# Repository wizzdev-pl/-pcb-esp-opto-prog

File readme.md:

# ESP Optoisolated Programmer

This repo contains design files of the ESP Optoisolated Programmer. It is helpful to develop software for products with and ESP microcontroller that are powered from 230V mains. It works for ESP32, ESP8266 and all other ESP modules.

For detailed description please read:
- [Schematic Description 1](https://wizzdev.pl/blog/esp32-optoisolated-programmer-schematic-description-1/)
- [Schematic Description 2](https://wizzdev.pl/blog/esp32-optoisolated-programmer-schematic-description-2/)
- [PCB Analysis 1](https://wizzdev.pl/blog/esp32-optoisolated-programmer-pcb-analysis-1-2/)
- [PCB Analysis 2](https://wizzdev.pl/blog/esp32-optoisolated-programmer-pcb-analysis-2/)
- [PCB Analysis 3](https://wizzdev.pl/blog/esp32-optoisolated-programmer-pcb-analysis-3/)

To open and edit design files, please use Kicad 6.

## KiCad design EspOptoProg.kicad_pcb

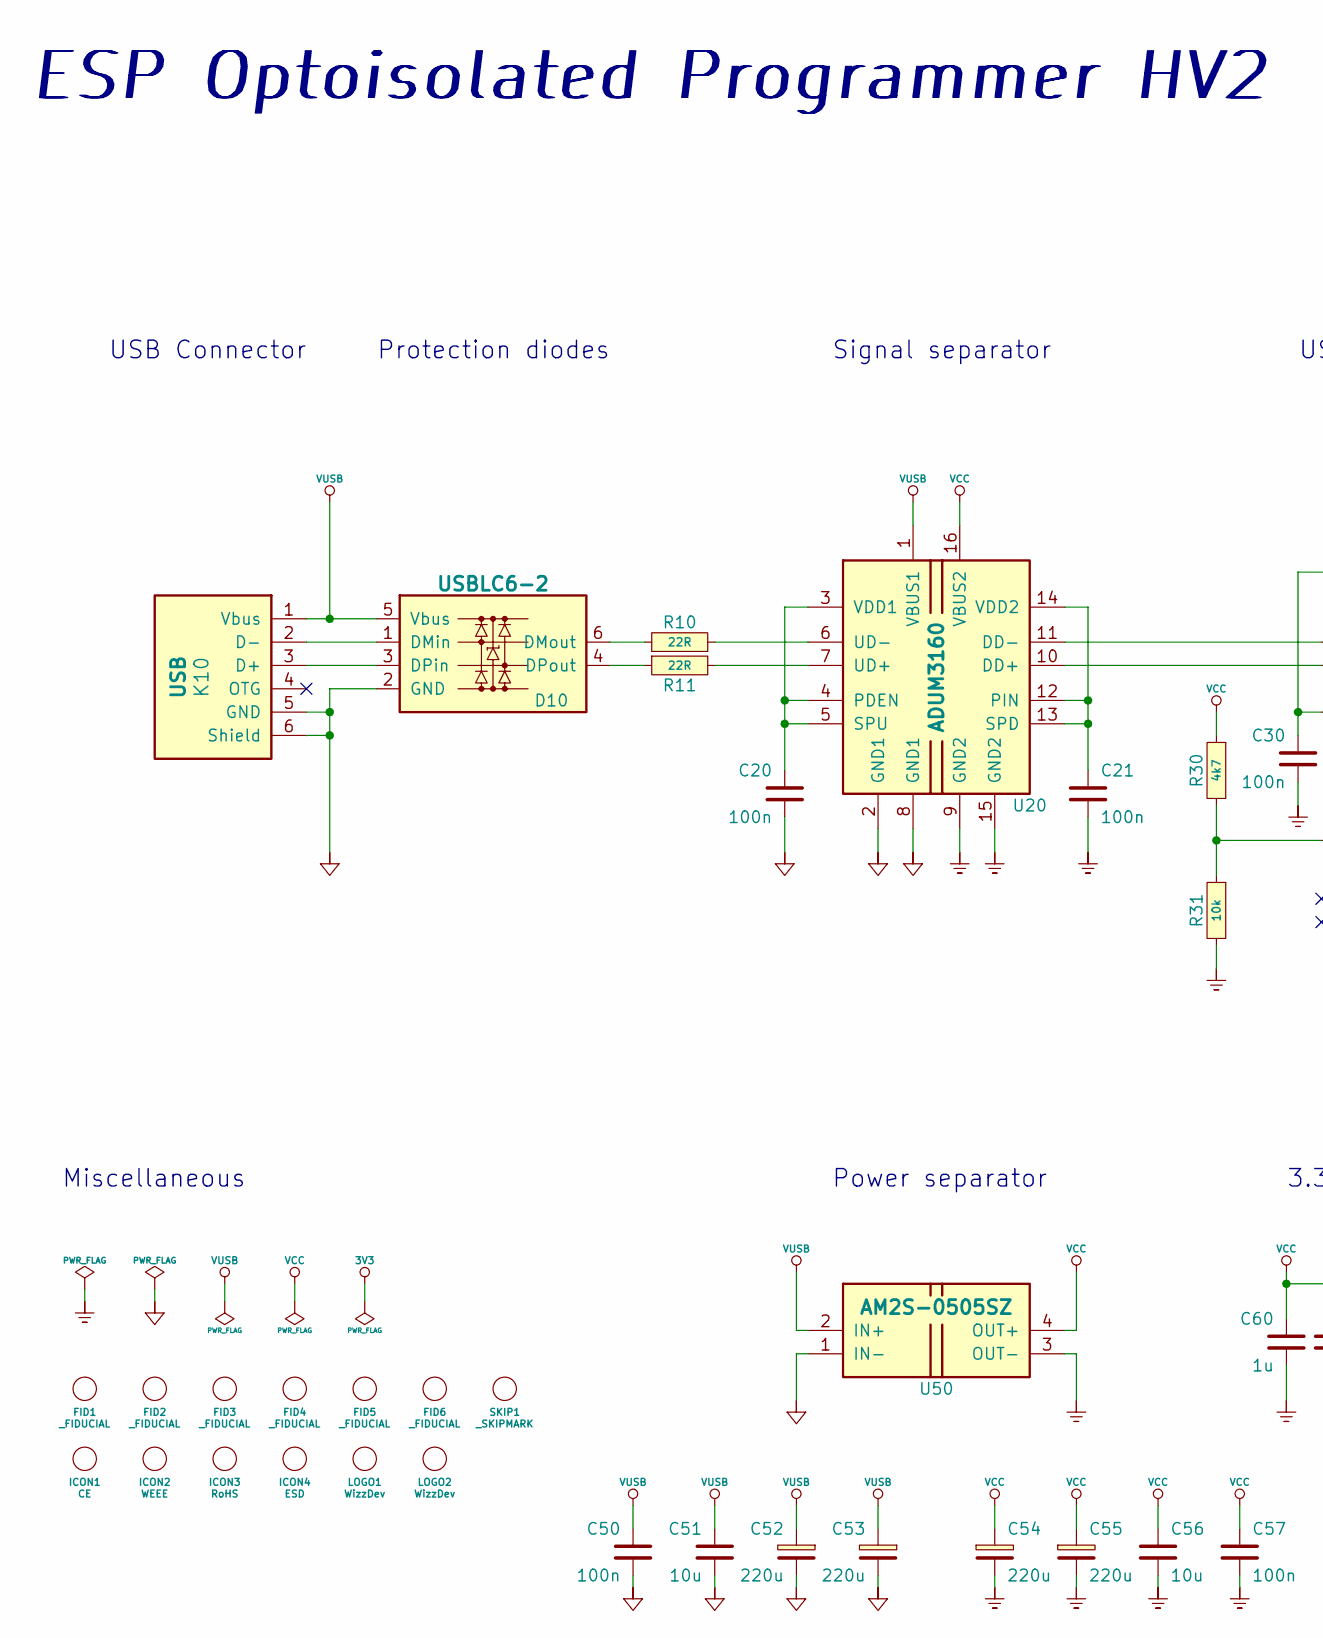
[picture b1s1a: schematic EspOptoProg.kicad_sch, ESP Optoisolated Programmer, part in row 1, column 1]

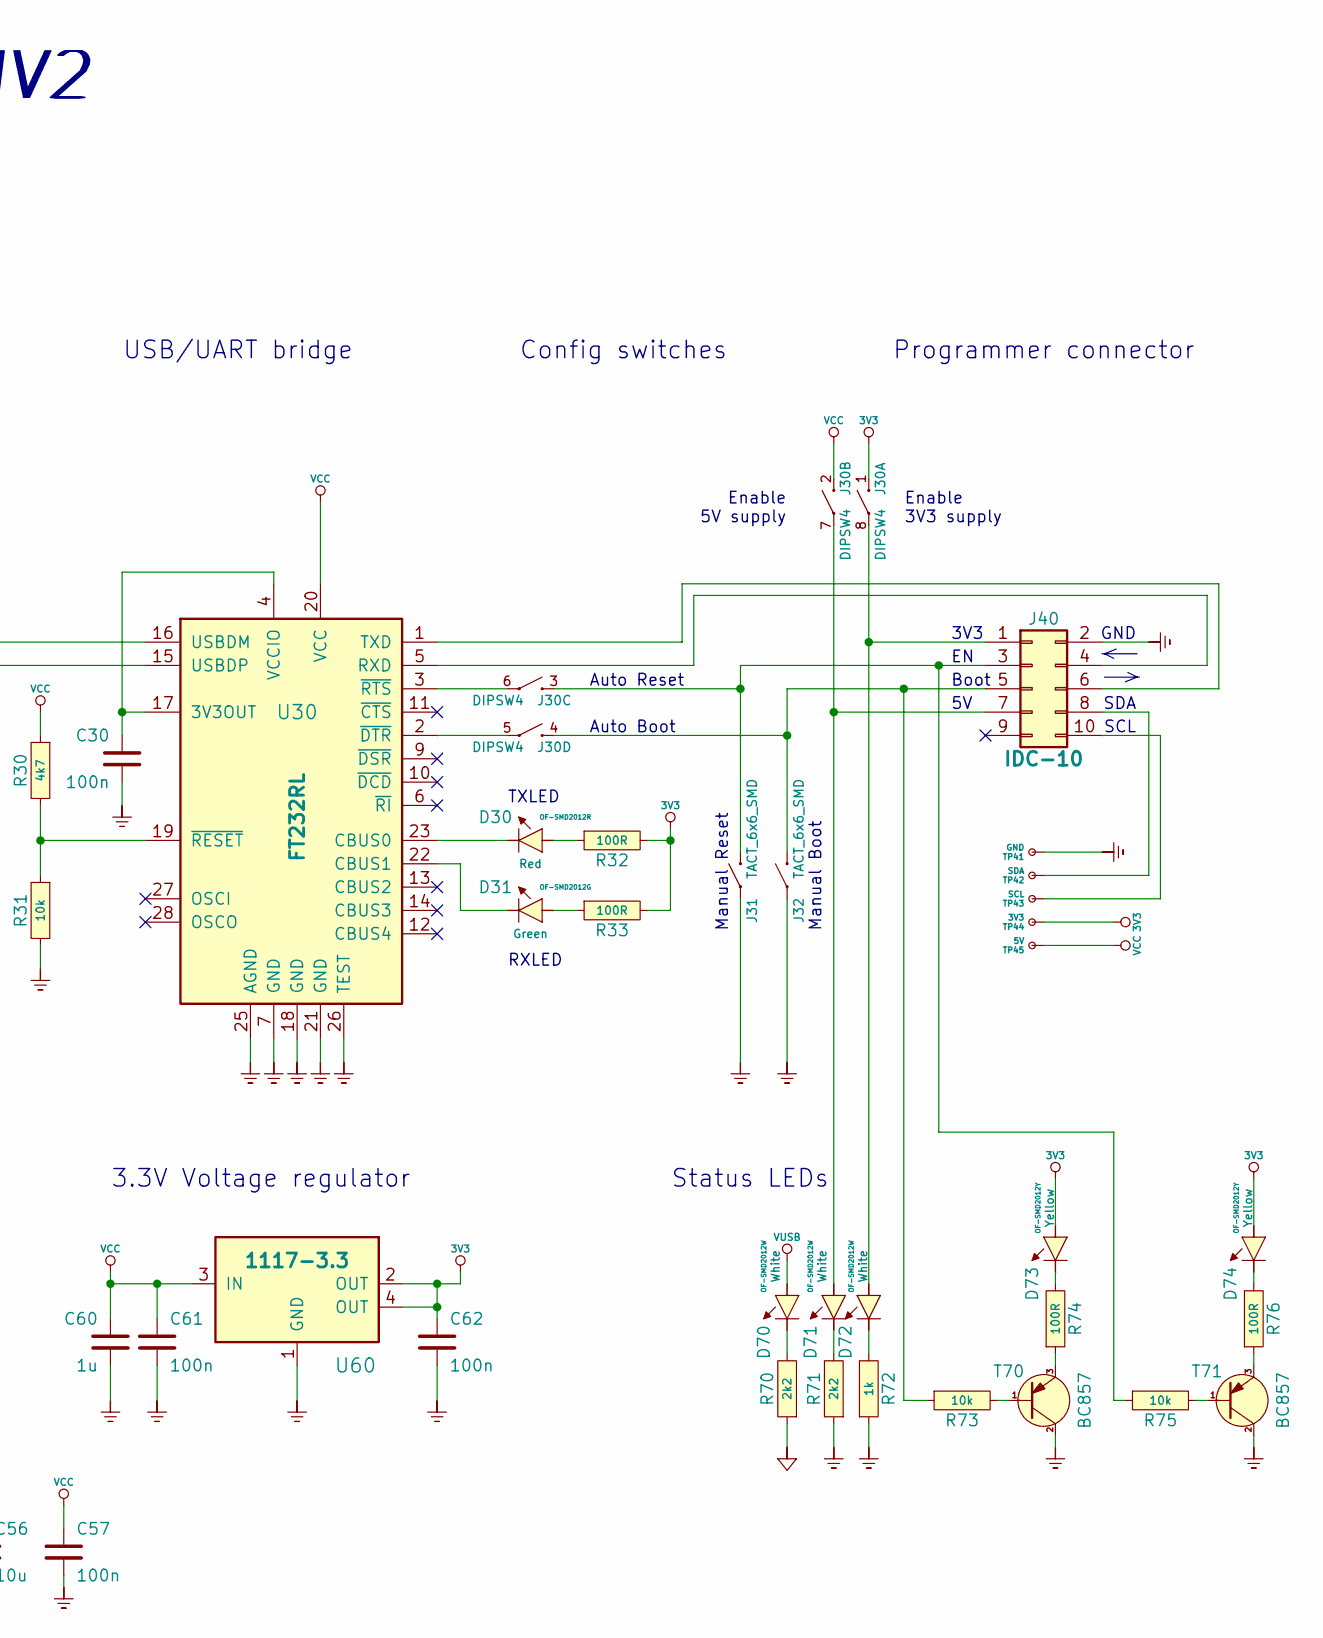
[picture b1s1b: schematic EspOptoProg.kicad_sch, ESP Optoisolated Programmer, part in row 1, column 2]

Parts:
C20, C21, C30, C50, C57, C61, C62: 100n; C_0603
C51, C56: 10u; C_0603
C52, C53, C54, C55: 220u; CP_Elec_6.3x7.7; Part SC1A227M6L07KVR SAMWHA
C60: 1u; C_0603
D10: USBLC6-2; SOT23-6
D30: OF-SMD2012R; LED_0805; Part OF-SMD2012R OPTOFLASH
D31: OF-SMD2012G; LED_0805; Part OF-SMD2012G OPTOFLASH
D70, D71, D72: OF-SMD2012W; LED_0805; Part OF-SMD2012W OPTOFLASH
D73, D74: OF-SMD2012Y; LED_0805
FID1, FID2, FID3, FID4, FID5, FID6: _FIDUCIAL; Fiducial_1.00mm_ring0.5mm
ICON1: CE; Logo_silk_CE_5x3.6mm
ICON2: WEEE; Logo_silk_WEEE_3.4x5mm
ICON3: RoHS; Logo_silk_ROHS_5x2.8mm
ICON4: ESD; ESD-Logo_6.6x6mm_SilkScreen
J30: DIPSW4; SW_DIP_SPSTx04_Slide_9.78x12.34mm_W7.62mm_P2.54mm; Part NDI-04H-V DIPTRONICS
J31, J32: TACT_6x6_SMD; Part TACTM-69N-F NINIGI
J40: IDC-10; IDC-Header_2x05_P2.54mm_Vertical
K10: USB; USB_Micro_B_Amphenol_10118194-0001LF_PIP; Part 10118194-0001LF
LOGO1: WizzDev; wizzdev-logo-part1
LOGO2: WizzDev; wizzdev-logo-part2
R10, R11: 22R; R_0603
R30: 4k7; R_0603
R31, R73, R75: 10k; R_0603
R32, R33, R74, R76: 100R; R_0603
R70, R71: 2k2; R_0603
R72: 1k; R_0603
SKIP1: _SKIPMARK; Skipmark_1.00mm
T70, T71: BC857; SOT23
TP41: GND; 1pin
TP42: SDA; 1pin
TP43: SCL; 1pin
TP44: 3V3; 1pin
TP45: 5V; 1pin
U20: ADUM3160; SOIC-16W_7.5x10.3mm_P1.27mm
U30: FT232RL; ssop-28
U50: AM2S-0505SZ; AMxS-xxxxSZ
U60: 1117-3.3; SOT223; Part 1117-3.3

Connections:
3V3: C62.1, D73.2 (A), D74.2 (A), J30.1, R32.2, R33.2, TP44.1, U60.2 (OUT), U60.4 (OUT)
GND: C21.2, C30.2, C54.2, C55.2, C56.2, C57.2, C60.2, C61.2, C62.2, J31.2, J32.2, J40.2, R31.2, R71.1, R72.1, T70.2, T71.2, TP41.1, U20.9 (GND2), U20.15 (GND2), U30.7 (GND), U30.18 (GND), U30.21 (GND), U30.25 (AGND), U30.26 (TEST), U50.3 (OUT-), U60.1 (GND)
GND2: C20.2, C50.2, C51.2, C52.2, C53.2, D10.2 (GND), K10.5 (GND), K10.6 (Shield), R70.1, U20.2 (GND1), U20.8 (GND1), U50.1 (IN-)
unnamed: C20.1, U20.3 (VDD1), U20.4 (PDEN), U20.5 (SPU)
unnamed: C21.1, U20.12 (PIN), U20.13 (SPD), U20.14 (VDD2)
unnamed: C30.1, U30.4 (VCCIO), U30.17 (3V3OUT)
unnamed: D10.1 (DMin), K10.2 (D-)
unnamed: D10.3 (DPin), K10.3 (D+)
unnamed: D10.4 (DPout), R11.1
unnamed: D10.6 (DMout), R10.1
unnamed: D30.1 (K), U30.23 (CBUS0)
unnamed: D30.2 (A), R32.1
unnamed: D31.1 (K), U30.22 (CBUS1)
unnamed: D31.2 (A), R33.1
unnamed: D70.1 (K), R70.2
unnamed: D71.1 (K), R71.2
unnamed: D71.2 (A), J30.7, J40.7
unnamed: D72.1 (K), R72.2
unnamed: D72.2 (A), J30.8, J40.1
unnamed: D73.1 (K), R74.2
unnamed: D74.1 (K), R76.2
unnamed: J30.3, J31.1, J40.3, R75.1
unnamed: J30.4, J32.1, J40.5, R73.1
unnamed: J30.5, U30.2 (~DTR)
unnamed: J30.6, U30.3 (~RTS)
unnamed: J40.4, U30.5 (RXD)
unnamed: J40.6, U30.1 (TXD)
unnamed: J40.8, TP42.1
unnamed: J40.10, TP43.1
unnamed: R10.2, U20.6 (UD-)
unnamed: R11.2, U20.7 (UD+)
unnamed: R30.2, R31.1, U30.19 (~RESET)
unnamed: R73.2, T70.1
unnamed: R74.1, T70.3
unnamed: R75.2, T71.1
unnamed: R76.1, T71.3
unnamed: U20.10 (DD+), U30.15 (USBDP)
unnamed: U20.11 (DD-), U30.16 (USBDM)
VCC: C54.1, C55.1, C56.1, C57.1, C60.1, C61.1, J30.2, R30.1, TP45.1, U20.16 (VBUS2), U30.20 (VCC), U50.4 (OUT+), U60.3 (IN)
VUSB: C50.1, C51.1, C52.1, C53.1, D10.5 (Vbus), D70.2 (A), K10.1 (Vbus), U20.1 (VBUS1), U50.2 (IN+)

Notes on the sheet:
SCL
ESP Optoisolated Programmer HV2
Signal separator
3.3V Voltage regulator
Auto Reset
USB/UART bridge
Enable 3V3 supply
Manual Boot
Enable 5V supply
Status LEDs
3V3
Boot
Manual Reset
Miscellaneous
Power separator
RXLED
GND
Auto Boot
Protection diodes
Programmer connector
Config switches
USB Connector
TXLED
SDA

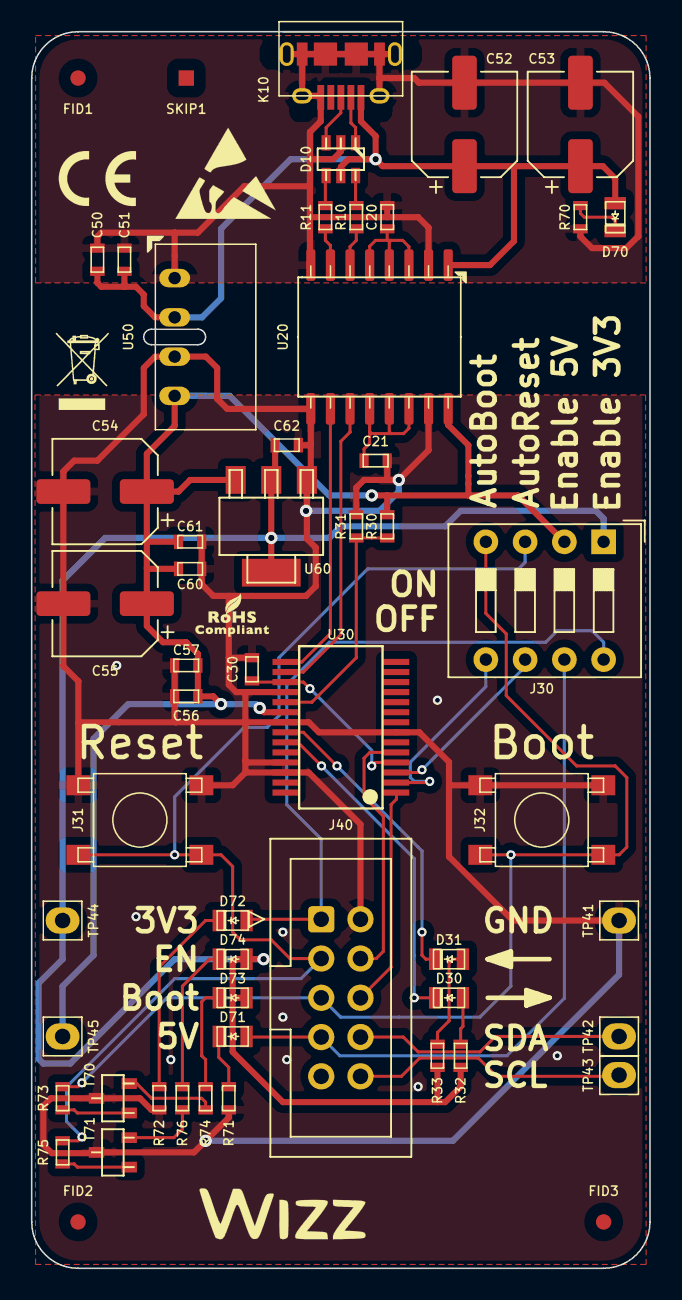
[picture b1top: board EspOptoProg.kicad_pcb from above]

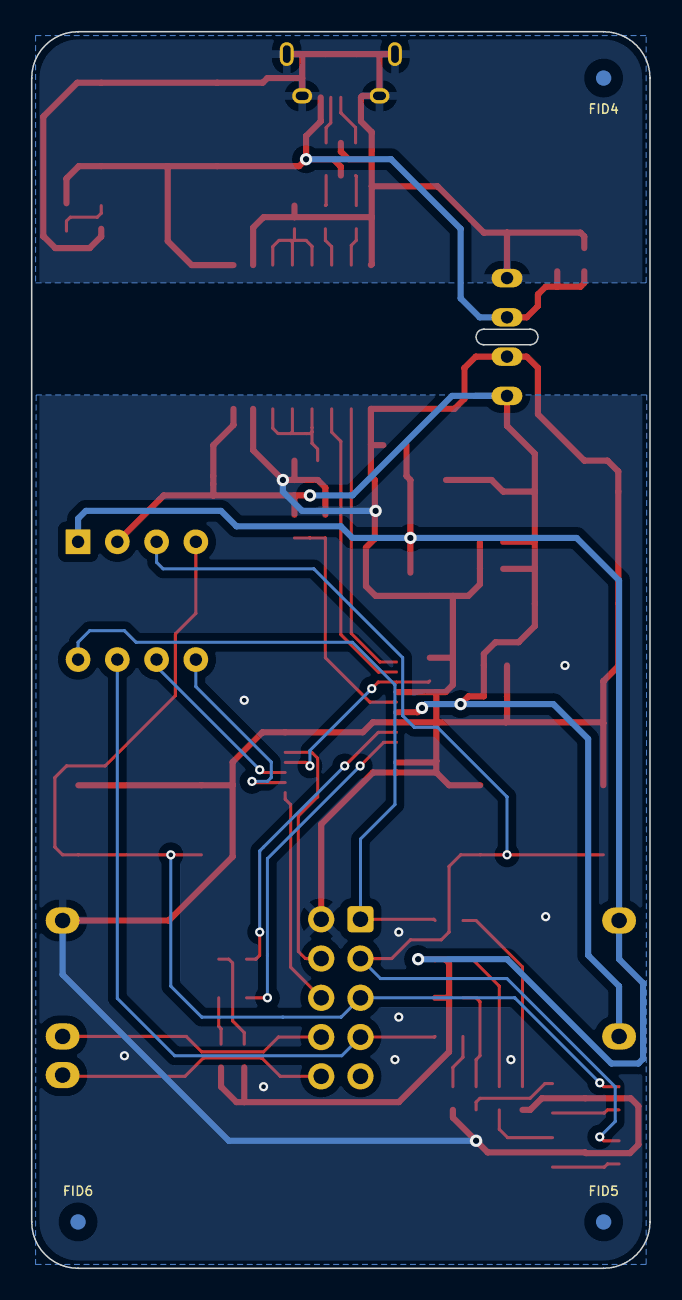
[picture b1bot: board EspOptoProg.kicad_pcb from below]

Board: 2 copper layers, 40.0 x 80.0 mm, 64 parts (3 on the bottom side), 40 nets.

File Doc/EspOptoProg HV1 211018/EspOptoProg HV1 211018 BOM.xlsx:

Id | Oznaczenie | Obudowa | IloĹ›Ä‡ | Oznaczenie | Dostawca i numer artykuĹ‚u
1 | LOGO1 | wizzdev-logo-part1 | 1 | WizzDev
2 | LOGO2 | wizzdev-logo-part2 | 1 | WizzDev
3 | U20 | SOIC-16W_7.5x10.3mm_P1.27mm | 1 | ADUM3160
4 | FID6,FID5,FID4,FID3,FID2,FID1 | Fiducial_1.00mm_ring0.5mm | 6 | _FIDUCIAL
5 | U30 | ssop-28 | 1 | FT232RL
6 | C53,C55,C54,C52 | CP_Elec_6.3x7.7 | 4 | 220u
7 | U50 | AMxS-xxxxSZ | 1 | AM2S-0505SZ
8 | J30 | SW_DIP_SPSTx04_Slide_9.78x12.34mm_W7.62mm_P2.54mm | 1 | DIPSW4
9 | J40 | IDC-Header_2x05_P2.54mm_Vertical | 1 | IDC-10
10 | C57,C62,C61,C50,C30 | C_0603 | 5 | 100n
11 | C56,C51 | C_0603 | 2 | 10u
12 | TP45 | 1pin | 1 | 5V
13 | TP44 | 1pin | 1 | 3V3
14 | T71,T70 | SOT23 | 2 | BC857
15 | SKIP1 | Skipmark_1.00mm | 1 | _SKIPMARK
16 | R76,R74,R71,R70,R33,R32 | R_0603 | 6 | 100R
17 | R75,R73,R31 | R_0603 | 3 | 10k
18 | D74,D73 | LED_0805 | 2 | OF-SMD2012Y
19 | TP43 | 1pin | 1 | SCL
20 | TP42 | 1pin | 1 | SDA
21 | TP41 | 1pin | 1 | GND
22 | U60 | SOT223 | 1 | 1117-3.3
23 | R72,R11,R10 | R_0603 | 3 | 22R
24 | R30 | R_0603 | 1 | 4k7
25 | R27,R26,R25,R24,R23,R22,R21,R20 | R_0603 | 8 | ?
26 | K10 | USB_Micro_B_Amphenol_10118194-0001LF_PIP | 1 | USB
27 | J32 | TACT_6x6_SMD | 1 | Boot
28 | J31 | TACT_6x6_SMD | 1 | Reset
29 | ICON4 | ESD-Logo_6.6x6mm_SilkScreen | 1 | ESD
30 | ICON3 | Logo_silk_ROHS_5x2.8mm | 1 | RoHS
31 | ICON2 | Logo_silk_WEEE_3.4x5mm | 1 | WEEE
32 | ICON1 | Logo_silk_CE_5x3.6mm | 1 | CE
33 | D72,D71,D70 | LED_0805 | 3 | OF-SMD2012W
34 | D31 | LED_0805 | 1 | OF-SMD2012G
35 | D30 | LED_0805 | 1 | OF-SMD2012R
36 | D10 | SOT23-6 | 1 | USBLC6-2
37 | C60 | C_0603 | 1 | 1u

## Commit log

2022-02-15 Moved repo to GitHub
